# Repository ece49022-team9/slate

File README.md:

# Slate

A portable voice assistant for everyday tasks. The ESP32 only records the microphones, drives the display and speaker, and talks to the cloud over Wi-Fi. Speech, the agent, its tools, and the browser all run on Modal. React handles setup and approvals.

## Code

| Path | Work |
| --- | --- |
| `firmware/` | ESP32 firmware |
| `server/slate/voice/` | Audio streaming, speech recognition and generation |
| `server/slate/agent/` | Model calls and task execution |
| `server/slate/browser/` | Browser sessions, tools and result checks |
| `server/slate/access/` | Accounts, pairing, permissions and credentials |
| `web/` | Setup, approvals and user control |
| `hardware/` | KiCad project and board sources |

One Python backend, deployed by [server/slate/cloud.py](server/slate/cloud.py). Keep model calls with the agent and permission checks in access. The web app never gets provider secrets.

## Setup

Install [uv](https://docs.astral.sh/uv/getting-started/installation/) and [Node 24](https://nodejs.org/), then:

```sh
make setup
make agent-setup   # download and verify the pinned Hermes source
make agent-login   # authorize Hermes with your Codex subscription
make cloud-setup   # create the slate-cloud Modal secret and upload the Hermes login
make cloud-deploy  # build and deploy the Slate service
```

`make cloud-deploy` runs one Modal container with the Slate service, the Hermes gateway, the device MCP server, and the browser supervisor, and writes the service URL to `.local/cloud.json` with a generated device token. Do not commit `.local`. `make cloud-logs` follows the container's logs. Hermes keeps its home on the container's disk; its login, memories, sessions, skills, scheduled jobs, and databases are copied to the `slate-hermes` volume every five minutes and on shutdown, and restored on start. `make cloud-setup` uploads the local Hermes login only when the volume has none, so later runs keep the cloud's refreshed tokens.

The Mac runs only the simulator: `make sim` boots the firmware in QEMU, gives it a network through QEMU's Ethernet model, and provisions it with the URL and token from `.local/cloud.json`.

For the browser client, run `make web` with `VITE_SLATE_URL=wss://<service host>` and `VITE_SLATE_DEVICE_TOKEN` set, then open [localhost:5173](http://127.0.0.1:5173), connect your microphone, and hold Talk.

`make check` runs lint, formatting, tests and the web build.

## Agent

Slate owns the voice connection, cancellation, and approval UI. Hermes owns the tool loop, session search, and persistent memory. Hermes has web search and extraction, image analysis, a terminal, files and Python code execution (all in a Modal sandbox), skills, task planning, delegated agents, scheduled jobs, account connections, memory, past-chat search, the browser, and the device SDK. Its clarifying-question tool has no channel through the API server, so Slate asks follow-up questions in its spoken reply. The `slate-guard` plugin in [hermes/slate-guard](hermes/slate-guard) sends any tool that would send a message or spend money to Slate's approval prompt; browser clicks are judged by the label of the element they hit, and Enter on a checkout page or a typed card number also needs approval. `uv run python scripts/check_agent.py --tools` checks web search, the Modal terminal, and a denied purchase on a test shop. Its source and dependencies are pinned in [experiments/agent.toml](experiments/agent.toml); the cloud image builds from the same verified source archive as the local `.local/hermes` cache.

The cloud container starts our own headless Chromium in a Modal sandbox, with authenticated CDP. Each sandbox lasts four hours; the supervisor checks it every minute, replaces it when it stops, and writes the new address to Hermes's `browser.cdp_url`, which Hermes rereads without a restart. `make agent` and `make browser` still run the same setup on the Mac for local evaluations.

With the cloud service deployed:

```sh
make agent-check   # exact model/provider route and conversation recall
make agent-e2e     # browser form, cross-session memory, simulated spoken turn
make agent-status # latest receipts
```

The browser check reads a random code from a synthetic page, fills its form, and checks the resulting DOM independently. The memory check creates and removes a synthetic preference. The voice check feeds a shared WAV through QEMU's mic into the firmware, which streams it to the cloud over its own TLS WebSocket; the check reads the transcript, the reply, and the amount of speech the firmware received from its serial log. Reply WAVs and detailed traces stay in `.local/agent-runs`.

`make agent-managed` checks the managed OpenAI Agents API directly with its key from `doppler run`. Managed browser tests use OpenAI's hosted desktop; Hermes uses our Modal browser. These are capability checks, not a controlled harness ranking.

`make voice-profile` profiles three voice turns against the cloud with the shared spoken fixture, using a Python client that speaks the firmware's socket protocol. Run `make voice-deploy` after changing speech code. Receipts include connection and turn setup, STT queues and decoding, agent first visible text, CSM first acoustic frame and decoded PCM, and the first non-silent reply audio the client receives. `REPEATS=5` changes the sample count. Profiling is opt-in; normal speech uses the PCM streamer without CUDA timing.

The device's clock and the server's clock are never subtracted from each other. End-to-audible runs from the client's end message to the first non-silent reply PCM it receives, so it includes the network both ways; server spans start when the server receives end. Generation and playback overlap, so the report does not subtract whole generation spans to estimate latency without inference. Provider queueing, prefill, and reasoning remain combined within agent TTFT. CSM's first acoustic frame is not playable audio. Compare initial and loaded-model calls separately; profiling can perturb execution.

Short live voice turns pass, but some device-confirmation replies still reach CSM's generation limit without an end token. The voice turn reports an error even when its device commands were acknowledged. These checks do not establish speech-model reliability; failures and successful trials are recorded separately in the experiment log.

Hermes receives one `execute_device_code` MCP entry point by default. Hermes's tool search is turned off so the model sees every enabled tool's schema directly instead of looking it up first. Its Python REPL exposes `device.set_orb(color, radius)`, `device.show_text(text)`, and `device.get_status()`. Pydantic validates requests and firmware receipts; each active voice turn has a separate capability scope. Successful commands include matching request IDs and firmware revisions. Failed programs report already-applied actions, and their REPL state is discarded. Text is limited to 64 printable ASCII characters; radius is 10–45 pixels.

Monty runs as a bounded subprocess of the device MCP server inside the cloud container, next to the device route, so a device call never leaves the container until it reaches the device's socket. It exposes only the listed methods and has no host files, network, or shell access. It does not replace the Chromium/Linux sandbox.

`SLATE_DEVICE_MODE=modal make cloud-deploy` runs the same Python SDK in CPython 3.12 inside a Modal Sandbox with internet access. The sandbox calls the public device route itself, with the turn's scope as a bearer token; the scope stops working when the turn ends. Each scope gets a fresh interpreter in a warm sandbox; a spare is kept ready for the next voice turn. A timeout or cancellation terminates the whole sandbox. `SLATE_DEVICE_MODE=tools` selects the three separate MCP tools for comparison.

```sh
make device-check         # real firmware commands and OLED SPI pixels
make device-code-check    # Monty against QEMU through the HTTP device route
make device-code-profile  # time tools and Monty; LAYER=agent for local Hermes turns
```

The profile runs one composed task (set the orb, show text, read status) against QEMU firmware. `LAYER=exec` times each runtime in-process and through the MCP stdio boundary. `LAYER=modal` runs Monty inside a Modal container against an in-container fake device. `LAYER=agent` restarts the local Hermes once per mode in ABC/CBA order and times full turns with fresh sessions. Results append to the experiment log.

The code-runtime check replaces the device socket with a fixture and verifies actual firmware state, pixels, partial failures, and expired scopes. Pressing Talk while a reply is in progress interrupts it: the client drops queued speech immediately, and the server revokes device access and cancels transcription, agent, and speech work before starting another turn. This is button-triggered interruption; automatic speech detection is not implemented. Managed final-answer deltas feed sentence synthesis; Hermes waits for its final answer because its run stream does not preserve the phase labels needed to safely speak deltas. Both paths stream CSM's decoded PCM. CSM uses its pinned upstream sampling defaults; reaching the generation limit without an end token remains an error.

Replies start with one or two sentences to speak; anything after a line containing only `---` is shown but not spoken. Work that will take more than about a minute runs as a background Hermes subagent, and the spoken turn ends once it starts. Slate watches the Hermes session for the result, runs a follow-up turn when no one is talking, and speaks it; the browser shows it as an announcement. Turns have no fixed time limit: Talk interrupts them, and Hermes stops subagents that stop making progress. `check_agent.py --tools` also checks the spoken summary and a background task.

`SLATE_HARNESS=hermes|openai` selects the backend. `SLATE_MODEL` selects the requested model; `SLATE_PROVIDER` selects Hermes's provider. Authorize that provider in the Hermes profile before changing it, and set the same model/provider on Hermes and the Slate server. Each completed run checks the observed route and rejects an unexpected fallback. API-compatible providers can be tested through upstream Hermes; model/tool compatibility still needs its own evaluation.

This is a single-user experiment. A new conversation does not isolate Hermes's persistent memory from other conversations in the same profile. Account isolation and enrollment need separate profiles before this serves multiple people.

## Evaluations

[experiments/progress.jsonl](experiments/progress.jsonl) is the append-only experiment log. It includes failures, source revisions, protocol identifiers, and denominators. Raw traces are private and ignored. Smoke checks and benchmark scores have separate scopes.

We use two external suites:

- [Sierra's τ benchmark](https://github.com/sierra-research/tau2-bench): policy-following, multi-turn task execution, and verified tool/state outcomes. The pinned repository now calls its protocol τ³; start with its airline text tasks. Retail references need auditing because upstream issue 499 reports incorrect expected results.
- [LongMemEval](https://github.com/xiaowu0162/LongMemEval): recall across timestamped conversations, updates, reasoning, and abstention. Use the cleaned V1 S dataset's complete histories with an isolated Hermes profile per question. The session-search arm uses Hermes's native search; full-context and no-memory arms show the retrieval gap. This pilot does not test learning memories through natural conversations.

```sh
make eval-setup
make eval-memory LIMIT=3
make eval-tau
make eval-tau-audit
```

Memory runs freeze the sample, dataset, model, source, and judge. They use the pinned upstream answer rubric with a GPT-6.1 Sol Responses judge; this is a custom judge protocol, not an official leaderboard result. `make eval-tau` runs the same seeded airline task through Hermes's MCP tools and the managed Agents API's function handlers, with the official environment and outcome evaluator. `TASK=18` selects the task; the default is one seeded sample, one trial per harness. `make eval-tau-audit` separately audits all airline gold references. Small pilots establish the pipeline and expose failures; they do not establish performance on the full suites or pass^4 reliability.

## Device connection

A device opens one WebSocket to `wss://<service>/api/device/socket` with `Authorization: Bearer <device token>`. Browsers, which cannot set that header, offer the subprotocols `slate` and the token instead. Control messages are JSON text frames; audio is binary 16-bit little-endian mono PCM.

| Direction | Message |
| --- | --- |
| Device → Slate | `{"type":"hello","rate":16000,"speaker_rate":16000}` first; the server resamples the mic to 24 kHz and reply speech to `speaker_rate` |
| Device → Slate | `{"type":"start"}`, binary mic frames, then `{"type":"end"}`; `{"type":"cancel"}` discards the turn |
| Device → Slate | `{"type":"live"}` starts a live call and `{"type":"hangup"}` ends it; mic frames stream the whole call |
| Device → Slate | `{"type":"receipt", ...}` for each command, with the firmware's state or an `error` |
| Slate → device | `turn`, `transcript` and `reply` (`text`, `final`), `tool`, `approval`, `error`, `cancelled`, each with `turn_id` |
| Slate → device | `{"type":"command","request_id","operation","arguments"}` for `set_orb`, `show_text`, `get_status` |
| Slate → device | binary reply speech at `speaker_rate`, sent about 0.2 s ahead of playback |
| Slate → device | `live` with `state` `started` or `ended` (`seconds`, maybe `error`), and `heard` and `said` word deltas, each with `call_id` |

A live call runs GPT-Live in the service. GPT-Live listens the whole time, decides when the user has finished and when to stop talking, and hands questions and tasks to Hermes. Each handoff gets the words said since the previous one, plus the device scope and approvals of a turn of its own; GPT-Live speaks the part of Hermes's answer before `---`. If GPT-Live's connection drops, the call starts a new session seeded with the conversation so far. Background results arriving during a call are given to GPT-Live to say. Its voice prompt is [live.md](server/slate/voice/live.md), and it needs `OPENAI_API_KEY`, which `make cloud-setup` copies from Doppler into the Modal secret.

`GET /api/voice/reports`, with the device token, returns timing, usage, and words for the connected device's recent turns and live calls, including a call in progress. `SLATE_PROFILE=1` on the service adds speech-model timings to turn reports.

One device is connected at a time; a new connection replaces the old one. Recordings are limited to two minutes. To send a recording as a device, without QEMU:

```sh
uv run python -m slate.voice simulate .local/voice-check.wav
```

It reads a mono 24 kHz, 16-bit WAV, streams it at 16 kHz in real time, prints the transcript and answer, and saves the returned speech to `.local/reply.wav`.

## Speech

[Kyutai STT](https://modal.com/docs/examples/streaming_kyutai_stt) and [Sesame CSM 1B](https://huggingface.co/docs/transformers/model_doc/csm) run in separate Modal apps, `slate-stt` and `slate-tts`. Both cache their weights and shut down after 60 seconds idle, so the first turn after a pause waits about 15–20 seconds for a GPU to start.

For a demo, `make voice-deploy DEMO=1` keeps both apps warm for 10 minutes after the last turn. Run `make voice-deploy` afterward to go back to 60 seconds.

Use the `sudarshan-1` Modal profile. CSM needs a Modal secret named `slate-huggingface` containing `HF_TOKEN`, with access to `sesame/csm-1b`.

```sh
make voice-deploy
make voice-check
```

The check generates speech, saves `.local/voice-check.wav`, and transcribes it. To use each model:

```sh
export MODAL_PROFILE=sudarshan-1
uv run python -m slate.voice tts "Slate is ready."
uv run python -m slate.voice stt .local/speech.wav
```

STT accepts mono 24 kHz, 16-bit PCM WAV files up to 120 seconds. TTS returns the same format and errors if it cannot finish within `--max-seconds` (default 15, max 30). CSM has no reference voice yet. Modal credentials stay on the backend.

## Firmware

The target is the original ESP32, on an ESP32-WROOM-32 dev board. The `esp32dev` image uses its Bluetooth radio. The `sim` image runs the same application with the NimBLE host connected over UART1 to the simulator:

```sh
make firmware   # build for the board
make firmware FIRMWARE_ENV=sim # build for QEMU
make flash      # write it to the board
make monitor    # serial console at 921600 baud
make pair SSID=<name> PASSWORD=<password> # set up a nearby board over Bluetooth
make sim-setup  # build the patched QEMU, once
make sim        # run the simulator image in QEMU with a browser preview
make sim-check  # run the simulator checks
make bench      # flash the board and run the hardware checks
```

An unconfigured device advertises as `Slate-XXXX`, where `XXXX` is the last two bytes of its Bluetooth address. Pair using the six-digit code on the OLED. Setup uses LE Secure Connections with an authenticated, encrypted link and does not retain a bond. Serial prints the code as `slate.ble: passkey NNNNNN`. `make pair` finds the board from the Mac, sends the Wi-Fi settings and the cloud address from `.local/cloud.json`, and waits for `done`; macOS asks for the code.

QEMU has no Bluetooth radio, so the simulator never appears to the Mac as a Bluetooth device. Instead, the simulator carries UART1 to `server/slate/bluetooth.py`, which acts as the controller and as a phone. `make sim-check` uses it to check advertising, the rejected unpaired write, a wrong code, pairing, saving both settings, shutdown, and the first message to a local cloud.

The setup service is `5a7e0001-6a1b-4c3e-9f5d-8b2c1e0d4a10`. Write one UTF-8 line of up to 240 bytes to characteristic `5a7e0002-6a1b-4c3e-9f5d-8b2c1e0d4a10`: `net wifi <ssid> <password>`, `net eth`, or `cloud <url> <token>`. Quote Wi-Fi fields containing spaces, as with serial provisioning. Read or subscribe to `5a7e0003-6a1b-4c3e-9f5d-8b2c1e0d4a10` for `ready`, `saved net`, `saved cloud`, `net up <ip>`, `net down`, `error <reason>`, and `done`. Both characteristics require pairing. The preferred ATT MTU is 256.

Send `!setup` over serial to reopen setup. The board reboots into setup if its controller memory has already been released; ESP-IDF cannot restore that memory during the same boot. The simulator reopens setup directly. Once network and cloud settings are saved, setup sends `done`, stops NimBLE, and returns the board's controller memory to the heap. Cloud operation then continues without a reboot. A configured board also releases controller memory at boot.

`make flash` and `make monitor` pick the board automatically when exactly one USB serial port is present. If several are connected, run `make ports` and pass `PORT=/dev/cu.<port>`. Over serial, send `0` through `5` for idle, listen, mute, transcribe, respond, or error; `l`, `r`, or `m` (while idle) to pick the left mic, right mic, or their mix; `a` or `x` to turn audio streaming on or off; `t` to play a one-second 440 Hz speaker test without blocking the mic or display; and `c` to start or end a live call. In listen, the firmware prints the mic's sample count, RMS, and peak every half second. With streaming on, it also sends the filtered mic audio as binary frames: a zero byte, a two-byte little-endian length, then 16-bit samples. Text never contains a zero byte, so the host can tell them apart. The ROM's boot messages use 115200 baud and look garbled at 921600.

The firmware reaches the cloud on its own. Provisioning is stored in flash and sent over serial: `!net wifi <ssid> <password>` on the board or `!net eth` in QEMU, then `!cloud <wss URL> <device token>`. `make provision SSID=<name> PASSWORD=<password>` sends both to a connected board using `.local/cloud.json`; names and passwords with spaces are not supported yet. Above the network driver the code is the same on both: TLS pinned to the ISRG roots, the WebSocket client, and the protocol above, in its own FreeRTOS task. Entering listen sends `start` and streams the selected mic; leaving it for transcribe sends `end`. The firmware logs `slate.transcript:`, `slate.reply:`, and `slate.reply.audio:`, and plays the reply speech on the speaker.

The mic schematic has two MP34DT01-M parts that share PDM clock and data: MK1 has L/R grounded (left slot) and MK2 has L/R tied high (right slot). The breadboard has one mic for now, on the left slot. I2S0 turns both slots into interleaved 16 kHz PCM. The firmware picks left, right, or an even mix, removes DC, and queues up to one second of audio. Mute and cancel clear the queue and the filter; transcribe keeps the queue so it can drain. The orb grows and brightens with the mic level while listening.

### Board description

[hardware/board.toml](hardware/board.toml) says which part is wired to which pin. [hardware/parts.toml](hardware/parts.toml) lists the parts we can use, with inventory counts from the class sheet, pin limits, supply range, and datasheet timing. `make board` checks the wiring and writes [firmware/main/board.h](firmware/main/board.h); `make firmware`, `make flash`, and `make check` run the same check. It rejects pins the chip lacks, input-only pins driving a part, flash/PSRAM/USB pins, shared pins, supply mismatches, and a PDM clock outside the mic's range. It warns about boot pins, SPI clocks above the datasheet limit, and wires long enough to ring (`wire_cm` on a device). To try another board, change `mcu`; `esp32-wrover-e`, for example, fails because its PSRAM uses GPIO16/17.

Current wiring: OLED clock GPIO18, MOSI GPIO23, CS GPIO5, D/C GPIO16, reset GPIO17 at 8 MHz; PDM clock GPIO26 and data GPIO36; speaker BCLK GPIO14, LRCLK GPIO25, and DIN GPIO27. The amplifier’s BCLK wire must use GPIO14 so it does not share the mic clock. GPIO39 is input-only on the ESP32 and cannot drive the PDM clock. At 16 MHz the breadboard corrupted frames (shifted, sheared and wrong-color fragments) whenever the orb was blue, magenta or white, so the OLED runs at 8 MHz, the Adafruit library's default, and refreshes at 25 fps (`frame_hz`). `hardware/parts.toml` lists 4.5 MHz for the breakout, so the checker still warns.

### Simulator

`make sim-setup` builds Espressif's QEMU with [sim/qemu.patch](sim/qemu.patch). The patch adds working GPIO output registers, an I2S0 receiver with DMA for the PDM mic, an I2S1 transmitter with DMA for the speaker, and a bridge to Python. It also fixes a QEMU bug that sent a stray command byte before every SPI transfer, which byte-swapped the OLED's pixels, and holds each SPI transfer busy for the bits it clocks out at the programmed rate, so a full OLED frame takes as long as it does on the bus (about 18 ms at 16 MHz, twice that at the current 8 MHz).

QEMU counts time by instructions (4 ns each, close to the ESP32's 240 MHz) instead of following the Mac's clock. The bridge sends pin changes, SPI bytes, and serial output to Python in order, and every emulated millisecond it stops and waits. Python answers with any serial keys or mic audio due at that moment, then lets it continue. Tests wait on emulated time, so the same inputs give the same run: `check_breadboard.py` runs twice and requires identical serial output and identical frames. The checks run as fast as the Mac allows; `make sim` and `make sim-voice` pace emulated time to the wall clock. QEMU emulates no Wi-Fi radio, so the simulated board uses QEMU's OpenCores Ethernet model, and QEMU's user networking sends its traffic through the Mac.

QEMU boots the exact image `make flash` writes. Python plays the parts on the breadboard: an SSD1351 that decodes the Adafruit library's SPI commands into display memory, and a mic that feeds PCM into the slot set by `slot` in `board.toml`. The host talks to the emulated serial port the same way it would talk to the board.

`make sim-check` runs the display, microphone, device, resource, and cloud checks against the normal image, and checks speaker output in both the dedicated and normal images:

- [check_breadboard.py](scripts/check_breadboard.py): two identical runs; the idle orb is drawn; a 440 Hz tone on the mic's slot reaches the meter within 5% RMS; the other slot stays silent; the orb grows and brightens while it hears sound; the panel runs at about 25 fps (`frame_hz`).
- [check_mic.py](scripts/check_mic.py): Hypothesis generates stereo audio for each channel. The streamed output must match an independent DC-filter calculation within one step, replay identically, and start clean after a muted turn. Failures are shrunk and saved for replay.
- [check_display.py](scripts/check_display.py): all six state colors, a blank panel on mute, a centered orb that fits the panel, smooth breathing, and 15 generated state sequences. It saves a frame to `.local/display-listen.png`.
- [check_speaker.py](scripts/check_speaker.py): a full second of 440 Hz stereo output through I2S1 DMA in the dedicated and normal firmware, followed by silence; checks channel agreement, frequency, and amplitude, then saves `.local/speaker.wav`. Run it alone with `make sim-speaker-check`.
- [check_resources.py](scripts/check_resources.py): while listening to a tone, the firmware's `slate.perf` report must show a frame (render plus SPI) within one refresh period (40 ms at `frame_hz = 25`), each 20 ms audio block processed in time, at least 32 KB of heap left with a 16 KB free block, and 512 bytes of stack left in every task.

QEMU runs the same 520 KB SRAM map, the WROOM-32's 4 MB flash, and no PSRAM, so heap and stack limits are the real ones. Its CPU is not cycle-accurate: every instruction costs 4 ns, with no flash cache misses or wait states. `make calibrate-sim` runs the same workload on the board and in QEMU and writes the hardware/QEMU timing ratios to `firmware/sim_calibration.toml`; the simulator check scales its timings by those ratios. Until then it reports timing as uncalibrated. `make bench` applies the same budgets to the board's own report.

`make sim` serves a breadboard view at [localhost:8010](http://127.0.0.1:8010). It draws the board and parts from `board.toml` with the wiring checker's warnings, animates each wire when its pin toggles or SPI bytes flow, and shows the live panel and the serial console. You can type keys, switch states, play a 440 Hz tone into the mic, or stream your computer's microphone into it. Click **Enable speaker audio** to hear firmware output through your computer, or **Test speaker output** to capture and play the full test tone. Speaker mute and volume are independent of mic input. Type `c` in the serial box to start or end a live call; the firmware streams the mic for the whole call and plays the call's speech on the speaker. Serial output goes to `.local/board-serial.log` and QEMU's own output to `.local/qemu.log`.

Speaker playback uses 16 kHz, 16-bit stereo PCM, resampled to your output device’s rate with bounded buffers. The test captures the complete tone before playback so slow emulation does not break it into beeps. `node tests/test_speaker_worklet.cjs` checks browser playback without audio hardware. QEMU checks DMA output; physical wiring, amplifier power, and I2S pin timing still need a hardware check. Rebuild with `make sim-setup` if your QEMU predates speaker support.

To send audio through the simulated firmware, the cloud agent, and the real speech services, run:

```sh
make sim-voice
```

`make duplex-profile` compares live calls with push to talk on the simulated firmware: the time from the end of the spoken question to Slate's first sound and to its answer, and, with "Wait, stop." spoken over a longer answer, how long Slate keeps talking. `ECHO=0.6` adds the speaker echo. `make cost-profile` runs the same 15-turn conversation through both and prices it; run the service with `SLATE_PROFILE=1` for the speech-model timings. Both use the deployed service, or `API_URL=http://127.0.0.1:8000` for one on the Mac, which the firmware reaches at 10.0.2.2. Results go to `experiments/progress.jsonl`.

Pass `INPUT=path/to/speech.wav` to use a different recording. The WAV must be 16-bit at 16, 24, or 48 kHz and at most 119 seconds. A stereo WAV fills both mic slots; a mono WAV fills the board's mic slot. `--channel` on the underlying Python command picks left (default), right, or mix. The command boots QEMU, waits for the firmware to connect to the cloud, plays the WAV into its mic model while holding listen, and prints the transcript, the reply, and how much speech the firmware received. Haptics are not started until their pins are confirmed.

The firmware plays reply speech on the MAX98357A. It sends its speaker rate in `hello`, and the cloud resamples CSM's 24 kHz speech to that rate. The firmware holds up to 250 ms of speech and starts playing once 160 ms has arrived, so short network delays do not cut the audio. `make sim-voice` saves what the simulated speaker pins carried to `.local/reply.wav`. In `make sim`, click **Enable speaker audio**, then **Use my microphone**, to talk to the full agent and hear it answer through the simulated amplifier.

### Bench

`make bench` flashes the board and runs the hardware version of the simulator checks over USB serial. It steps through all six states, reads the frame rate the board reports, records a second of background sound, then plays a 440 Hz tone through the Mac's speaker. The mic's streamed audio must be at least three times louder than the background, and 440 Hz must be at least ten times stronger than 300 Hz, 600 Hz, 1 kHz, and 2 kHz. Put the board near the speaker and turn the volume up. The script cannot see the panel, so check by eye that the orb changes color with each state. Serial output goes to `.local/bench-serial.log`.

To run the same turn on the real board after `make provision`, add `--port`; the Mac plays the WAV aloud and the board streams what its mic hears over Wi-Fi:

```sh
MODAL_PROFILE=sudarshan-1 uv run python -m slate.voice firmware .local/voice-check.wav --port /dev/cu.usbserial-2120
```

[Proposal](https://docs.google.com/document/d/1dz02PJORUFB1m--cltmt9tKI_VPXVcO9dAPNODxkFbo/edit) · [Work split](https://notes.granola.ai/t/a576ba7f-ef74-42ac-b631-dfefc260f884-008umkv4)

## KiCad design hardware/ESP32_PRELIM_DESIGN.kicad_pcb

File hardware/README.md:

# Hardware

Keep the team's native schematic and board sources here, including any project-specific libraries needed to open them. The current bring-up board uses an ESP32-WROOM-32 module; its microphone, OLED, and haptic GPIO wiring is not yet confirmed. Record the pin map alongside these sources when it is known. Firmware configuration must follow that hardware revision.

Open `ESP32_PRELIM_DESIGN.kicad_pro` with KiCad 10. The preliminary schematic was imported unchanged from the team's `hw` and `fw` branches. The PCB file is an empty board, not a placed or routed design. Circuit correctness and fabrication readiness have not been established.

KiCad 10.0.5 can export the schematic netlist, but reports annotation errors. Resolve those in the schematic editor before treating the netlist as ready for board work.

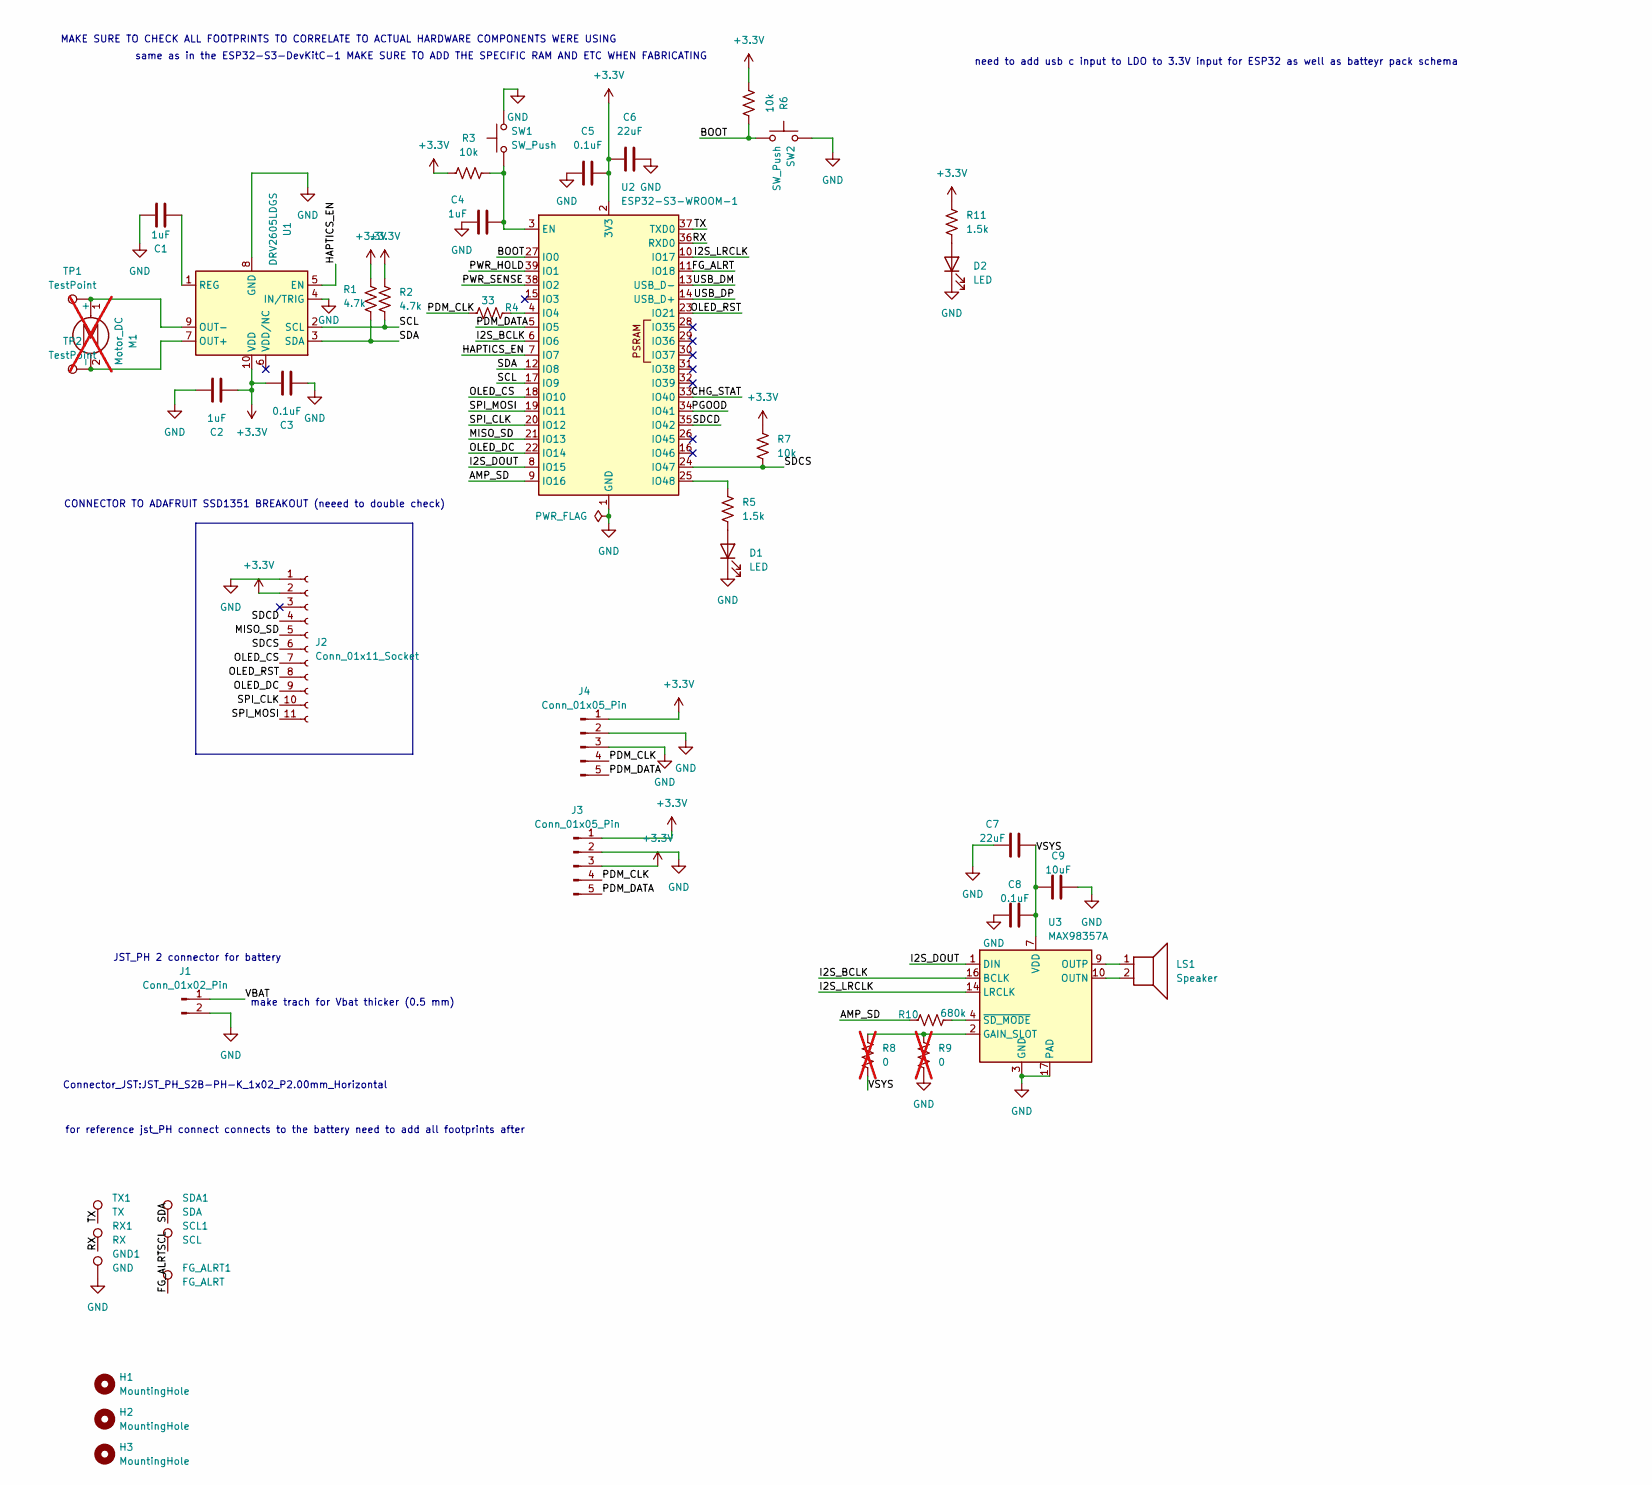
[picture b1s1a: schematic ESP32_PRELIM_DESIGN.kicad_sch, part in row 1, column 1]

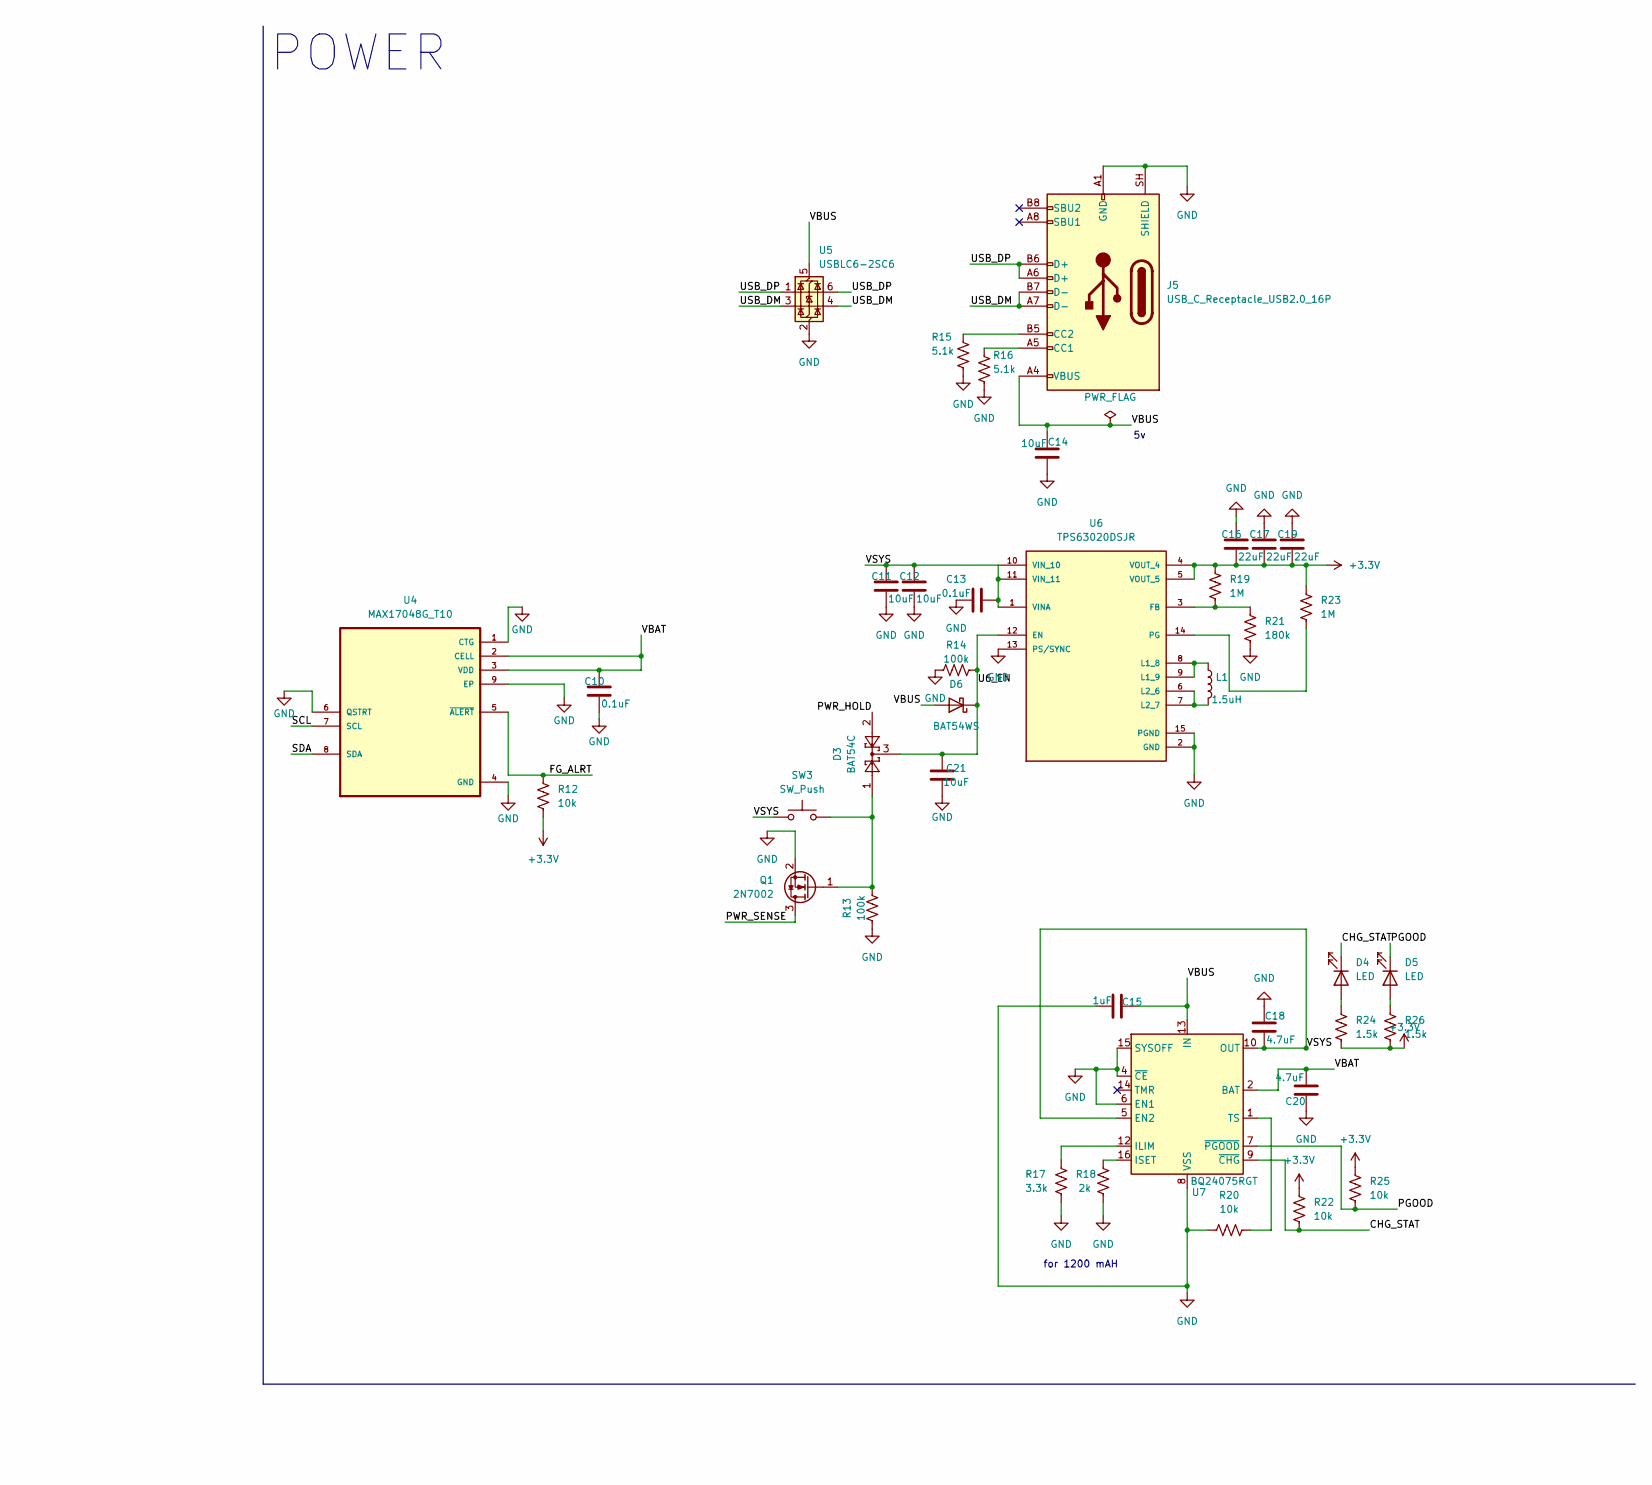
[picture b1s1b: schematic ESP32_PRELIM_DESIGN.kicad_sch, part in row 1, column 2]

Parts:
C1, C2, C4, C15: 1uF; C_0805_2012Metric_Pad1.18x1.45mm_HandSolder
C3, C5, C8, C10, C13: 0.1uF; C_0805_2012Metric_Pad1.18x1.45mm_HandSolder
C6, C7, C16, C17, C19: 22uF; C_1206_3216Metric_Pad1.33x1.80mm_HandSolder
C9, C11, C12, C14, C21: 10uF; C_0805_2012Metric_Pad1.18x1.45mm_HandSolder
C18, C20: 4.7uF; C_0805_2012Metric_Pad1.18x1.45mm_HandSolder
D1, D2, D4, D5: LED; LED_0805_2012Metric_Pad1.15x1.40mm_HandSolder
D3: BAT54C; SOT-23
D6: BAT54WS; D_SOD-323_HandSoldering
FG_ALRT1: FG_ALRT; TestPoint_Pad_D2.0mm
GND1: GND; TestPoint_Pad_D2.0mm
H1, H2, H3: MountingHole; MountingHole_2.2mm_M2
J1: Conn_01x02_Pin; JST_PH_S2B-PH-K_1x02_P2.00mm_Horizontal
J2: Conn_01x11_Socket; PinSocket_1x11_P2.54mm_Vertical
J3, J4: Conn_01x05_Pin; JST_PH_S5B-PH-K_1x05_P2.00mm_Horizontal
J5: USB_C_Receptacle_USB2.0_16P; USB_C_Receptacle_GCT_USB4105-xx-A_16P_TopMnt_Horizontal
L1: 1.5uH; L_Coilcraft_XAL4020-XXX
LS1: Speaker; Molex_PicoBlade_53261-0271_1x02-1MP_P1.25mm_Horizontal
M1: Motor_DC; not fitted
Q1: 2N7002; SOT-23
R1, R2: 4.7k; R_0805_2012Metric_Pad1.20x1.40mm_HandSolder
R3, R6, R7, R12, R20, R22, R25: 10k; R_0805_2012Metric_Pad1.20x1.40mm_HandSolder
R4: 33; R_0805_2012Metric_Pad1.20x1.40mm_HandSolder
R5, R11, R24, R26: 1.5k; R_0805_2012Metric_Pad1.20x1.40mm_HandSolder
R8, R9: 0; R_0805_2012Metric_Pad1.20x1.40mm_HandSolder; not fitted
R10: 680k; R_0805_2012Metric_Pad1.20x1.40mm_HandSolder
R13, R14: 100k; R_0805_2012Metric_Pad1.20x1.40mm_HandSolder
R15, R16: 5.1k; R_0805_2012Metric_Pad1.20x1.40mm_HandSolder
R17: 3.3k; R_0805_2012Metric_Pad1.20x1.40mm_HandSolder
R18: 2k; R_0805_2012Metric_Pad1.20x1.40mm_HandSolder
R19, R23: 1M; R_0805_2012Metric_Pad1.20x1.40mm_HandSolder
R21: 180k; R_0805_2012Metric_Pad1.20x1.40mm_HandSolder
RX1: RX; TestPoint_Pad_D2.0mm
SCL1: SCL; TestPoint_Pad_D2.0mm
SDA1: SDA; TestPoint_Pad_D2.0mm
SW1, SW2, SW3: SW_Push; SW_SPST_CK_KMS2xxGP
TP1, TP2: TestPoint; TestPoint_Pad_1.5x1.5mm
TX1: TX; TestPoint_Pad_D2.0mm
U1: DRV2605LDGS; TSSOP-10_3x3mm_P0.5mm
U2: ESP32-S3-WROOM-1
U3: MAX98357A; TQFN-16-1EP_3x3mm_P0.5mm_EP1.23x1.23mm
U4: MAX17048G_T10; SON50P200X200X80-9N
U5: USBLC6-2SC6; SOT-23-6
U6: TPS63020DSJR; IC_TPS63020DSJR
U7: BQ24075RGT; QFN-16-1EP_3x3mm_P0.5mm_EP1.7x1.7mm

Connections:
+3.3V: C2.1, C3.2, C5.2, C6.2, C16.1, C17.1, C19.1, J2.2, J3.1, J3.3, J4.1, R1.2, R2.2, R3.1, R6.1, R7.1, R11.1, R12.2, R19.1, R22.1, R23.1, R24.2, R25.1, R26.2, U1.10 (VDD), U2.2 (3V3), U6.4 (VOUT_4), U6.5 (VOUT_5)
/AMP_SD: R10.1, U2.9 (IO16)
/BOOT: R6.2, SW2.1, U2.27 (IO0)
/CHG_STAT: D4.1 (K), R22.2, U2.33 (IO40), U7.9 (~CHG)
/FG_ALRT: FG_ALRT1.1 (1_1), R12.1, U2.11 (IO18), U4.5 (~ALERT)
/HAPTICS_EN: U1.5 (EN), U2.7 (IO7)
/I2S_BCLK: U2.6 (IO6), U3.16 (BCLK)
/I2S_DOUT: U2.8 (IO15), U3.1 (DIN)
/I2S_LRCLK: U2.10 (IO17), U3.14 (LRCLK)
/MISO_SD: J2.5, U2.21 (IO13)
/OLED_CS: J2.7, U2.18 (IO10)
/OLED_DC: J2.9, U2.22 (IO14)
/OLED_RST: J2.8, U2.23 (IO21)
/PDM_CLK: J3.4, J4.4, R4.2
/PDM_DATA: J3.5, J4.5, U2.5 (IO5)
/PGOOD: D5.1 (K), R25.2, U2.34 (IO41), U7.7 (~PGOOD)
/PWR_HOLD: D3.2, U2.39 (IO1)
/PWR_SENSE: Q1.3 (D), U2.38 (IO2)
/RX: RX1.1 (1_1), U2.36 (RXD0)
/SCL: R2.1, SCL1.1 (1_1), U1.2 (SCL), U2.17 (IO9), U4.7 (SCL)
/SDA: R1.1, SDA1.1 (1_1), U1.3 (SDA), U2.12 (IO8), U4.8 (SDA)
/SDCD: J2.4, U2.35 (IO42)
/SDCS: J2.6, R7.2, U2.24 (IO47)
/SPI_CLK: J2.10, U2.20 (IO12)
/SPI_MOSI: J2.11, U2.19 (IO11)
/TX: TX1.1 (1_1), U2.37 (TXD0)
/U6_EN: C21.1, D3.3, D6.1 (K), R14.2, U6.12 (EN)
/USB_DM: J5.A7 (D-), J5.B7 (D-), U2.13 (USB_D-), U5.3 (I/O2), U5.4 (I/O2)
/USB_DP: J5.A6 (D+), J5.B6 (D+), U2.14 (USB_D+), U5.1 (I/O1), U5.6 (I/O1)
/VBAT: C10.2, C20.2, J1.1, U4.2 (CELL), U4.3 (VDD), U7.2 (BAT), U7.3 (BAT)
/VBUS: C14.1, C15.1, D6.2 (A), J5.A4 (VBUS), J5.A9 (VBUS), J5.B4 (VBUS), J5.B9 (VBUS), U5.5 (VBUS), U7.13 (IN)
/VSYS: C7.1, C8.2, C9.2, C11.2, C12.2, C13.2, C18.2, R8.2, SW3.1, U3.7 (VDD), U3.8 (VDD), U6.1 (VINA), U6.10 (VIN_10), U6.11 (VIN_11), U7.5 (EN2), U7.10 (OUT), U7.11 (OUT)
GND: C1.2, C2.2, C3.1, C4.1, C5.1, C6.1, C7.2, C8.1, C9.1, C10.1, C11.1, C12.1, C13.1, C14.2, C15.2, C16.2, C17.2, C18.1, C19.2, C20.1, C21.2, D1.1 (K), D2.1 (K), GND1.1 (1_1), J1.2, J2.1, J3.2, J4.2, J4.3, J5.A1 (GND), J5.A12 (GND), J5.B1 (GND), J5.B12 (GND), J5.SH (SHIELD), Q1.2 (S), R9.2, R13.1, R14.1, R15.2, R16.2, R17.2, R18.2, R20.2, R21.2, SW1.2, SW2.2, U1.4 (IN/TRIG), U1.8 (GND), U2.1 (GND), U2.40 (GND), U2.41 (GND), U3.3 (GND), U3.11 (GND), U3.15 (GND), U3.17 (PAD), U4.1 (CTG), U4.4 (GND), U4.6 (QSTRT), U4.9 (EP), U5.2 (GND), U6.2 (GND), U6.13 (PS/SYNC), U6.15 (PGND), U7.4 (~CE), U7.6 (EN1), U7.8 (VSS), U7.15 (SYSOFF), U7.17 (VSS)
unnamed: D1.2 (A), R5.2
unnamed: D2.2 (A), R11.2
unnamed: D4.2 (A), R24.1
unnamed: D5.2 (A), R26.1
unnamed: J5.A5 (CC1), R16.1
unnamed: J5.B5 (CC2), R15.1
unnamed: D3.1, Q1.1 (G), R13.2, SW3.2
unnamed: M1.2 (-), TP2.1 (1_1), U1.7 (OUT+)
unnamed: M1.1 (+), TP1.1 (1_1), U1.9 (OUT-)
unnamed: C1.1, U1.1 (REG)
unnamed: C4.2, R3.2, SW1.1, U2.3 (EN)
unnamed: R4.1, U2.4 (IO4)
unnamed: R5.1, U2.25 (IO48)
unnamed: R8.1, R9.1, U3.2 (GAIN_SLOT)
unnamed: LS1.2, U3.10 (OUTN)
unnamed: LS1.1, U3.9 (OUTP)
unnamed: R10.2, U3.4 (~SD_MODE)
unnamed: R19.2, R21.1, U6.3 (FB)
unnamed: L1.1, U6.8 (L1_8), U6.9 (L1_9)
unnamed: L1.2, U6.6 (L2_6), U6.7 (L2_7)
unnamed: R23.2, U6.14 (PG)
unnamed: R17.1, U7.12 (ILIM)
unnamed: R18.1, U7.16 (ISET)
unnamed: R20.1, U7.1 (TS)

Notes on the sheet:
CONNECTOR TO ADAFRUIT SSD1351 BREAKOUT (neeed to double check)
same as in the ESP32-S3-DevKitC-1 MAKE SURE TO ADD THE SPECIFIC RAM AND ETC WHEN FABRICATING
need to add usb c input to LDO to 3.3V input for ESP32 as well as batteyr pack schema
POWER
MAKE SURE TO CHECK ALL FOOTPRINTS TO CORRELATE TO ACTUAL HARDWARE COMPONENTS WERE USING
for reference jst_PH connect connects to the battery need to add all footprints after
JST_PH 2 connector for battery
for 1200 mAH
Connector_JST:JST_PH_S2B-PH-K_1x02_P2.00mm_Horizontal
make trach for Vbat thicker (0.5 mm)

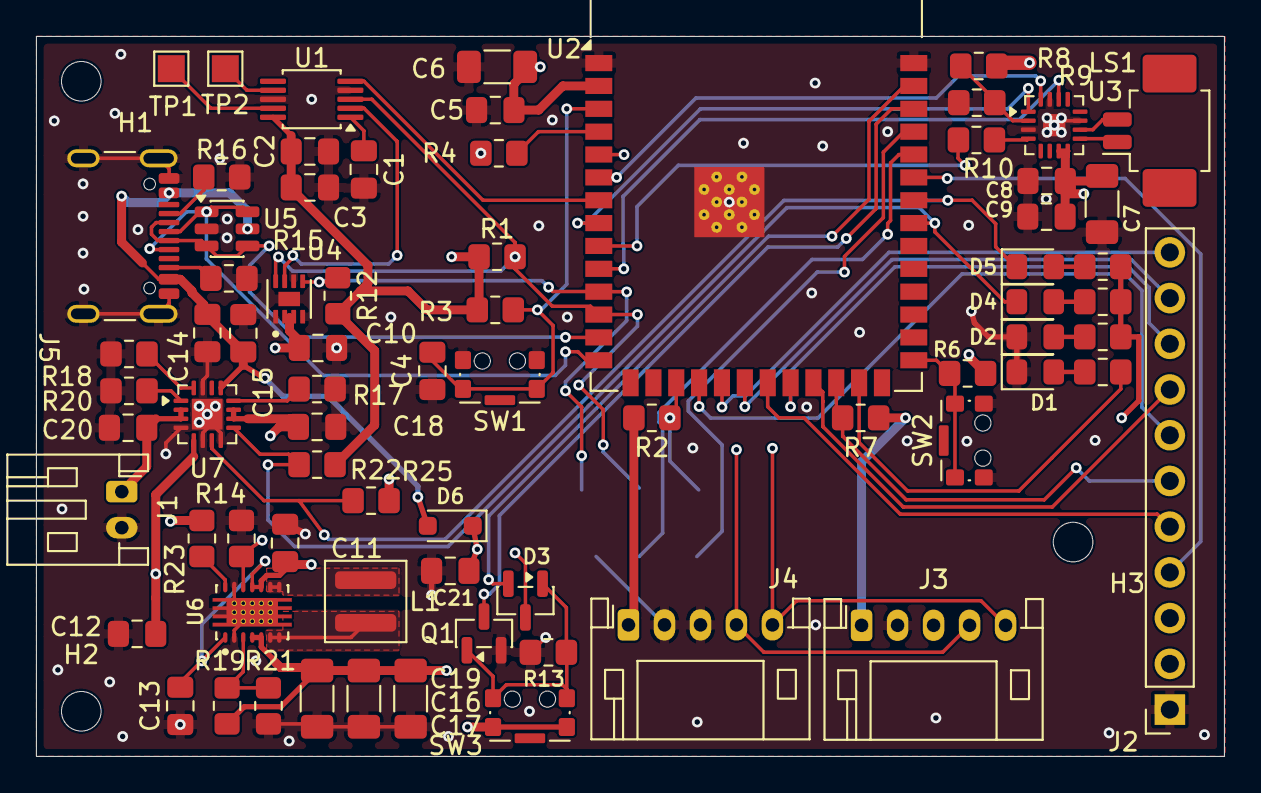
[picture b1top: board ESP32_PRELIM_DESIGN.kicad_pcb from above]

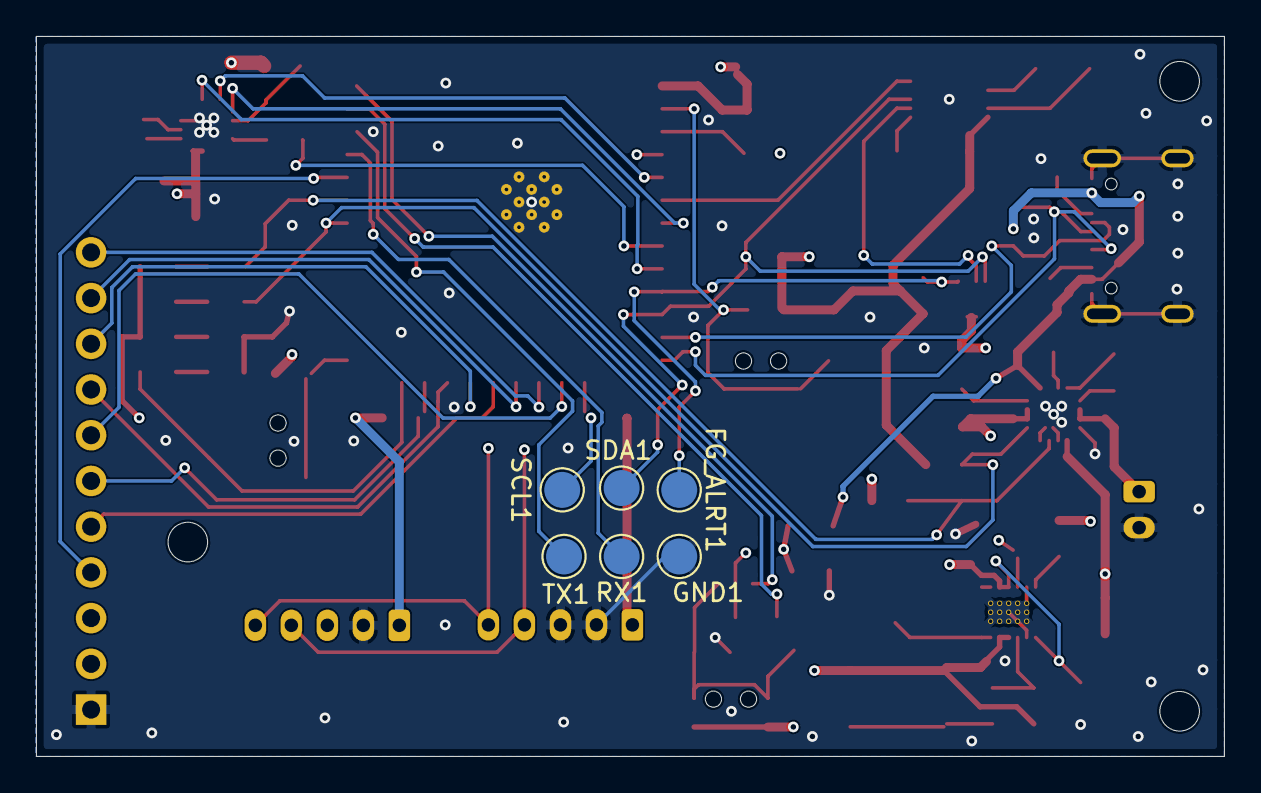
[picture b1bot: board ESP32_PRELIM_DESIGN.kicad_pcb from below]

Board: 4 copper layers, 66.0 x 40.0 mm, 82 parts (6 on the bottom side), 57 nets.
